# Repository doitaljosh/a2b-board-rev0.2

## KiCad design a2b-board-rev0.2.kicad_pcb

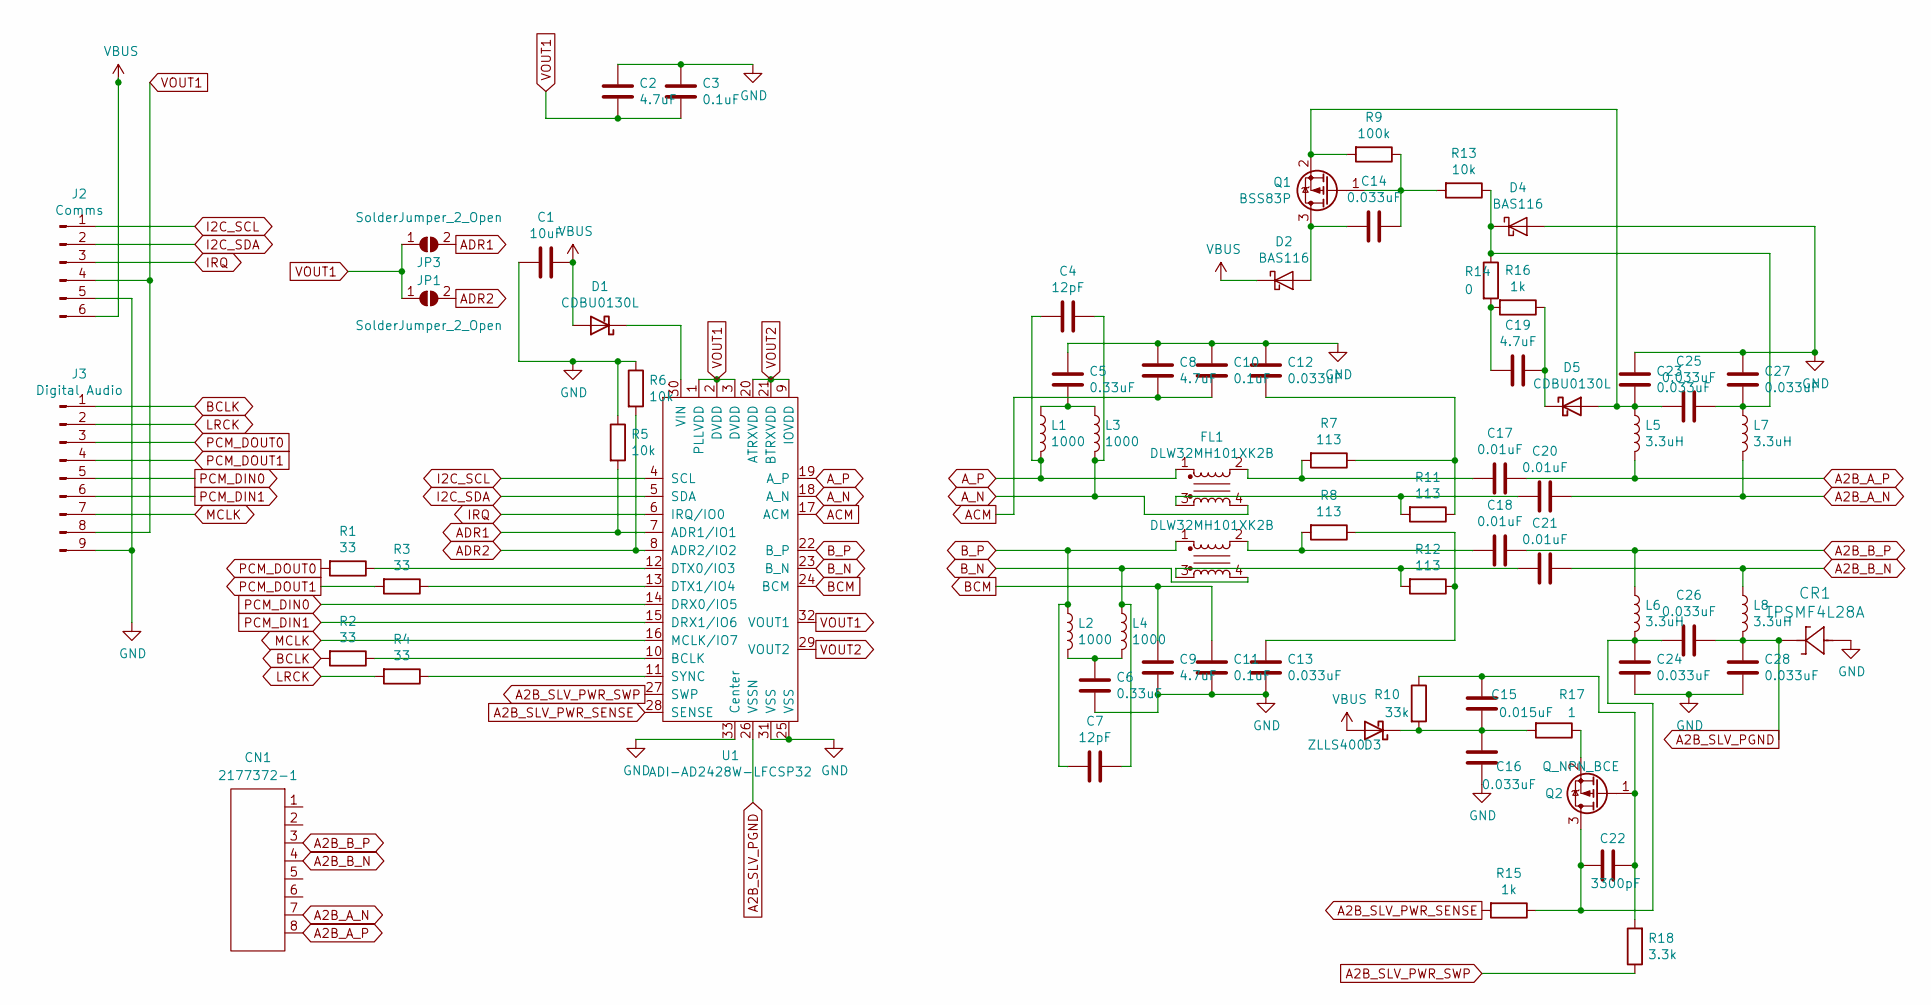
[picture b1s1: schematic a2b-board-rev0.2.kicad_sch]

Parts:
C1: 10uF; C_0603_1608Metric
C2, C8, C9, C19: 4.7uF; C_0603_1608Metric
C3, C10, C11: 0.1uF; C_0402_1005Metric
C4, C7: 12pF; C_0402_1005Metric
C5, C6: 0.33uF; C_0603_1608Metric
C12, C13: 0.033uF; C_0603_1608Metric
C14, C16, C23, C24, C25, C26, C27, C28: 0.033uF; C_0402_1005Metric
C15: 0.015uF; C_0402_1005Metric
C17, C18, C20, C21: 0.01uF; C_0402_1005Metric
C22: 3300pF; C_0402_1005Metric
CN1: 2177372-1; 2177372-3
CR1: TPSMF4L28A; D_SOD-123F
D1, D5: CDBU0130L; D_SOD-523
D2, D4: BAS116; D_SOT-23_ANK
D3: ZLLS400; D_SOD-323
FL1, FL2: DLW32MH101XK2B; FIL_DLW32MH101XK2L
J2: Comms; PinHeader_1x06_P2.54mm_Vertical
J3: Digital Audio; PinHeader_1x09_P2.54mm_Vertical
JP1, JP3: SolderJumper_2_Open; SolderJumper-2_P1.3mm_Open_RoundedPad1.0x1.5mm
L1, L2, L3, L4: 1000; L_0402_1005Metric
L5, L6, L7, L8: 3.3uH; L_0402_1005Metric
Q1: BSS83P; SOT-23
Q2: Q_NPN_BCE; SOT-23
R1, R2, R3, R4: 33; R_0402_1005Metric
R5, R6, R13: 10k; R_0402_1005Metric
R7, R8, R11, R12: 113; R_0612_1632Metric
R9: 100k; R_0402_1005Metric
R10: 33k; R_0402_1005Metric
R14: 0; R_0402_1005Metric
R15, R16: 1k; R_0402_1005Metric
R17: 1; R_0402_1005Metric
R18: 3.3k; R_0402_1005Metric
U1: ADI-AD2428W-LFCSP32; LFCSP-32-1EP_5x5mm_P0.5mm_EP3.1x3.1mm

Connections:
A2B_A_N: C20.1, CN1.7, L7.2
A2B_A_P: C17.1, CN1.8, L5.2
A2B_B_N: C21.1, CN1.4, L8.1
A2B_B_P: C18.1, CN1.3, L6.1
A2B_SLV_PGND: C26.1, C28.1, CR1.1, L8.2, U1.26 (VSSN)
A2B_SLV_PWR_SENSE: R15.2, U1.28 (SENSE)
A2B_SLV_PWR_SWP: R18.1, U1.27 (SWP)
ACM: C8.2, C10.2, U1.17 (ACM)
ADR1: JP3.2 (B), R5.2, U1.7 (ADR1/IO1)
ADR2: JP1.2 (B), R6.2, U1.8 (ADR2/IO2)
A_N: C4.1, FL1.4, L3.2, U1.18 (A_N)
A_P: C4.2, FL1.1, L1.2, U1.19 (A_P)
BCLK: J3.1, R2.2
BCM: C9.1, C11.1, U1.24 (BCM)
B_N: C7.1, FL2.4, L4.1, U1.23 (B_N)
B_P: C7.2, FL2.1, L2.1, U1.22 (B_P)
GND: C1.1, C2.1, C3.1, C5.1, C6.2, C8.1, C9.2, C10.1, C11.2, C12.1, C13.2, C16.1, C23.1, C24.2, C27.1, C28.2, CR1.2, D4.2 (A), J2.5, J3.9, R5.1, R6.1, U1.25 (VSS), U1.31 (VSS), U1.33 (Center)
I2C_SCL: J2.1, U1.4 (SCL)
I2C_SDA: J2.2, U1.5 (SDA)
IRQ: J2.3, U1.6 (IRQ/IO0)
LRCK: J3.2, R4.2
MCLK: J3.7, U1.16 (MCLK/IO7)
unnamed: C5.2, L1.1, L3.1
unnamed: C6.1, L2.2, L4.2
unnamed: C12.2, R7.1, R11.1
unnamed: C13.1, R8.1, R12.1
unnamed: C17.2, FL1.2, R7.2
unnamed: C18.2, FL2.2, R8.2
unnamed: C19.2, R14.2, R16.2
unnamed: C20.2, FL1.3, R11.2
unnamed: C21.2, FL2.3, R12.2
unnamed: D1.1 (K), U1.30 (VIN)
unnamed: C14.2, D2.2 (A), Q1.3 (D)
unnamed: C15.1, C16.2, D3.1 (K), R10.2, R17.2
unnamed: C25.1, C27.2, D4.1 (K), L7.1, R13.1, R14.1
unnamed: C23.2, C25.2, D5.2 (A), L5.1, Q1.2 (S), R9.2
unnamed: C19.1, D5.1 (K), R16.1
unnamed: C14.1, Q1.1 (G), R9.1, R13.2
unnamed: C22.2, C24.1, C26.2, L6.2, Q2.3 (D), R15.1
unnamed: C15.2, C22.1, Q2.1 (G), R10.1, R18.2
unnamed: Q2.2 (S), R17.1
unnamed: R2.1, U1.10 (BCLK)
unnamed: R1.1, U1.12 (DTX0/IO3)
unnamed: R3.1, U1.13 (DTX1/IO4)
unnamed: R4.1, U1.11 (SYNC)
PCM_DIN0: J3.5, U1.14 (DRX0/IO5)
PCM_DIN1: J3.6, U1.15 (DRX1/IO6)
PCM_DOUT0: J3.3, R1.2
PCM_DOUT1: J3.4, R3.2
VBUS: C1.2, D1.2 (A), D2.1 (K), D3.2 (A), J2.6
VOUT1: C2.2, C3.2, J2.4, J3.8, JP1.1 (A), JP3.1 (A), U1.1 (PLLVDD), U1.2 (DVDD), U1.3 (DVDD), U1.32 (VOUT1)
VOUT2: U1.9 (IOVDD), U1.20 (ATRXVDD), U1.21 (BTRXVDD), U1.29 (VOUT2)

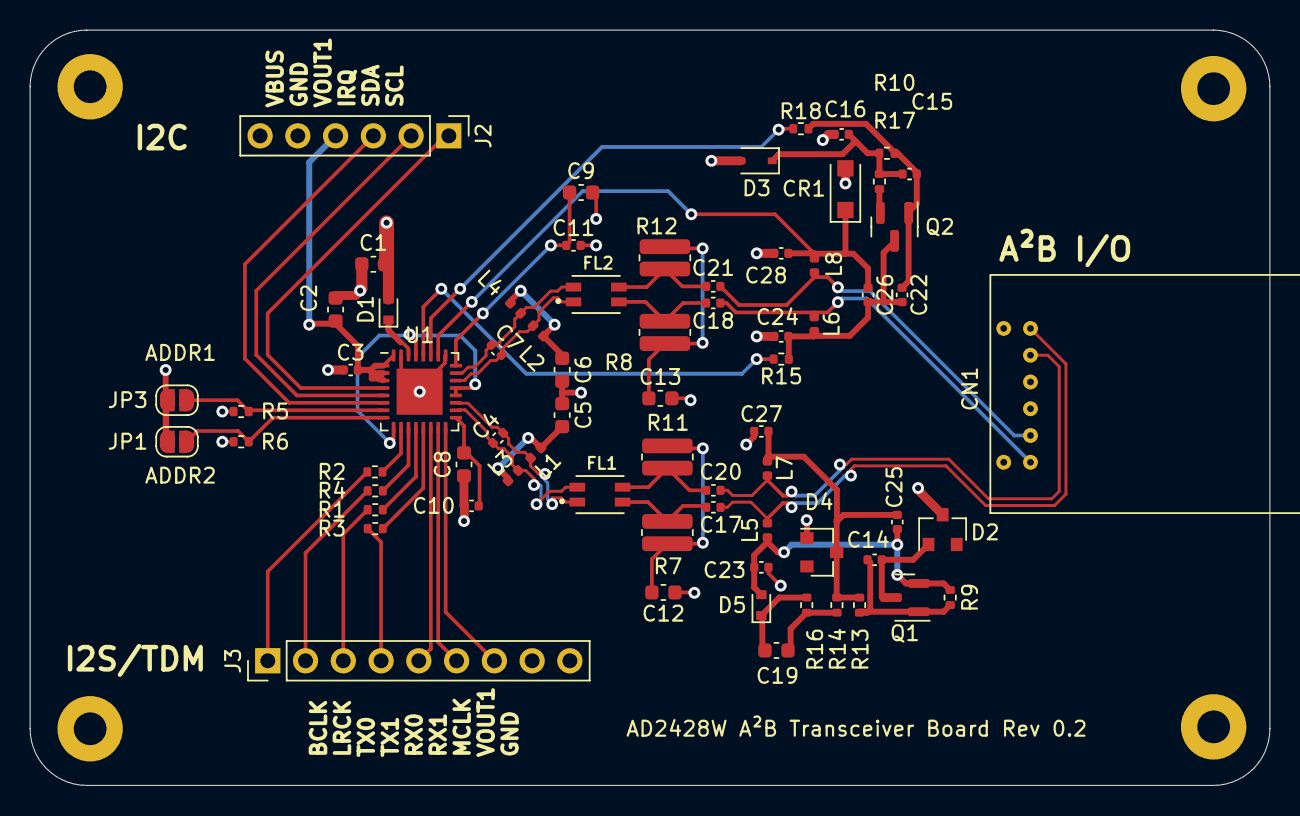
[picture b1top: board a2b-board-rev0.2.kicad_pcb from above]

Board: 4 copper layers, 83.4 x 50.8 mm, 72 parts (0 on the bottom side), 52 nets.

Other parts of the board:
H1, H1#2: MountingHole_2.2mm_M2_Pad

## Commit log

2025-05-08 Add PDF files for viewing schematic and boardview
